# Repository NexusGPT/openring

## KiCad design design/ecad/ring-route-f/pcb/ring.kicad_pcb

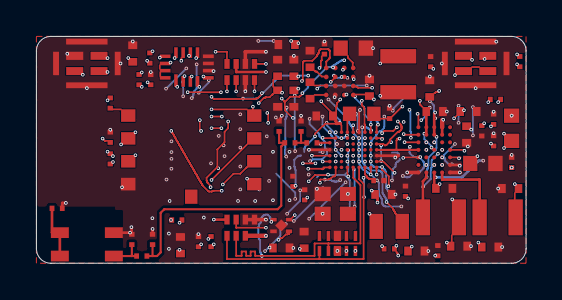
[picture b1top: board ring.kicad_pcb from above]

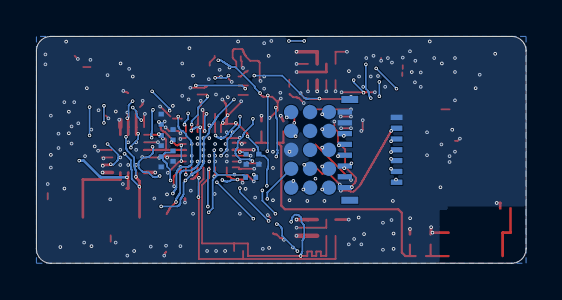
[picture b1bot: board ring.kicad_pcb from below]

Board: 4 copper layers, 27.2 x 12.6 mm, 100 parts (24 on the bottom side), 84 nets.

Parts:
ANT1: 2450AT18D0100001E; ANT_Johanson_2450AT18D0100001E_3.2x1.6
C1, C2, C5, C61, C72, C80, C81, C82: 100nF; Chip_0201
C3: 1.2pF; Chip_0201
C4, C22, C25, C74, C75, C78, C79, C83, C84: 10uF; Chip_0402
C6: 4.7uF; Chip_0201
C7, C10, C14: 2.2uF; Chip_0201
C11, C21, C26, C27: 4.7uF; Chip_0402
C12: 0.5pF; Chip_0201
C13, C89: DNP; Chip_0201
C23, C60, C85: 2.2uF; Chip_0402
C24, C88: 10uF; Chip_0603
C28, C29: 22uF; Chip_0402
C31, C32: 1uF; Chip_0201
C35, C36: 1nF C0G; Chip_0402
C71: 1.0uF 25V; Chip_0402
C73: 1.0uF; Chip_0201
C76, C77: 1.0nF; Chip_0201
C86, C87: 1.0uF; Chip_0402
FB1: 120R@100MHz; Chip_0201
J1: FH35C-15S-0.3SHW(50); FPC_Hirose_FH35C-15S-0.3SHW
J_BAND_A: flex tail A (joystick side) 8 pads; J_BAND_A_BOARD
J_BAND_B: flex tail B (other side) 7 pads; J_BAND_B_BOARD
L1: 4.7uH; L_TDK_MLZ1608_1.6x0.8
L2: 3.6nH; Chip_0201
L3: 4.7nH; Chip_0201
L4: 3.3nH; Chip_0201
L10, L71, L72: 2.2uH; L_Murata_1269AS-H_2.5x2.0
LT1: 0R; Chip_0201
R1: 2.2R; Chip_0603
R2: 220R; Chip_0201
R31, R32, R61: 100R; Chip_0201
R57, R58: 4.7k; Chip_0201
R60, R63, R64, R65, R71: 47k; Chip_0201
R62, R66: 100k; Chip_0201
R72: 150k; Chip_0201
TP1, TP3, TP4, TP5, TP6, TP8, TP9, TP11, TP12, TP14, TP15, TP17, TP18, TP19, TP21: pad; TESTPAD_0.8
U1: nRF54LM20A; WLCSP-61_nRF54LM20A-CAAA
U2: nPM1304; WLCSP-35_nPM1304-CAAA
U3: CSNP32GCR01-BOW; LGA-9_CSNP32GCR01-BOW_8.0x6.2
U4: SGM38046; WLCSP-16_SGM38046_2.0x2.0_P0.5
U5, U6: SPK0641HT4H-1; LGA-8_Knowles_SPK0641HT4H-1_3.0x4.0
U9: TPD4E05U06; USON-10_TPD4E05U06DQA
U10: SN74AXC4T774; UQFN-16_SN74AXC4T774RSV_1.8x2.6
U11: TLV75530P 3.0V; X2SON-4_TLV755xxPDQN_1.0x1.0
X1: 32MHz; XTAL_Kyocera_CX2016DB_2.0x1.6
X2: 32.768kHz; XTAL_TXC_9HT11_2.0x1.2

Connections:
ANT1_NODE: L2.1, U1.C1
ANT2_NODE: C3.1, L2.2, L3.1
ANT3_NODE: C12.1, C89.1, L3.2, L4.1
ANT_TRIM: ANT1.2, ANT1.3, LT1.1
BTN_REC: J_BAND_A.5, U1.H2
DBG_TX: TP1.1, U1.B4
DCC: L1.1, U1.A5
DECA: C7.1, C14.1, FB1.2, U1.A8, U1.B2
DECD: C6.1, FB1.1, L1.2, U1.A6
ELVDD: C25.1, J1.2, U4.D3
ELVSS: C28.1, C29.1, J1.1, U4.D4
GND: ANT1.4, C1.2, C2.2, C3.2, C4.2, C5.2, C6.2, C7.2, C10.2, C11.2, C12.2, C13.2, C14.2, C21.2, C22.2, C24.2, C25.2, C26.2, C27.2, C28.2, C29.2, C31.2, C32.2, C35.2, C36.2, C60.2, C61.2, C71.2, C72.2, C73.2, C74.2, C75.2, C76.2, C77.2, C78.2, C79.2, C80.2, C81.2, C82.2, C83.2, C84.2, C85.2, C86.2, C87.2, C88.2, C89.2, J1.13, J1.14, J1.15, J_BAND_A.6, J_BAND_A.8, J_BAND_B.2, J_BAND_B.7, LT1.2, R2.2, R62.2, R66.2, R71.2, R72.2, TP18.1, U1.A7, U1.D3, U1.E1, U1.F10, U2.A6, U2.A7, U2.E7, U3.4, U4.A3, U4.B2, U4.B3, U5.3, U5.5, U5.6, U5.7, U5.8, U6.5, U6.6, U6.7, U6.8, U9.3, U9.8, U10.6, U10.7, U10.8, U11.2, U11.5, X1.2
JOY_DOWN: J_BAND_A.2, U1.G2
JOY_LEFT: J_BAND_A.3, U1.G1
JOY_RIGHT: J_BAND_A.4, U1.G10
JOY_UP: J_BAND_A.1, U1.H1
LCD_CS: J1.9, U1.F7
LCD_DCX: J1.11, U1.G7
LCD_MOSI: J1.12, U1.G8
LCD_RST: J1.8, U1.H5
LCD_SCK: J1.10, U1.G9
LCD_TE: J1.7, U1.F4
MIC1_DATA: R31.1, U5.1
MIC2_DATA: R32.1, U6.1
MIC_A_CLK: U1.F1, U5.2, U6.2
MIC_A_DATA: R31.2, R32.2, U1.F2
MIC_B_DATA: TP21.1, U1.D7
MOTOR: R61.1, U1.F6
MOT_EN: R61.2, R62.1, U11.3
NRESET: TP5.1, U1.E2
NTC: J_BAND_B.3, U2.D3
OLED_PWR_EN: R66.1, U1.F9, U4.C2
PMIC_INT: U1.D8, U2.D6
PMIC_SCL: R58.1, U1.E7, U2.E3
PMIC_SDA: R57.1, U1.B8, U2.E5
RF_FEED: ANT1.1, C13.1, L4.2
SDC_CS: R65.1, U3.2, U10.10
SDC_MISO: R60.1, U3.6, U10.9
SDC_MOSI: U3.5, U10.11
SDC_SCK: U3.3, U10.12
SD_CS: U1.D9, U10.3
SD_DAT1: R63.1, U3.7
SD_DAT2: R64.1, U3.1
SD_MISO: U1.D10, U10.4
SD_MOSI: U1.B10, U10.2
SD_SCK: U1.A9, U10.1
SGM_AVDD: C26.1, U4.D2
SGM_AVIN: C22.1, U4.A2
SGM_C1N: C23.2, U4.B4
SGM_C1P: C23.1, U4.A4
SGM_SW1: L10.1, U4.B1
SGM_SW2: L10.2, U4.C1
SGM_VON: C27.1, U4.C4
SGM_VOUT: C24.1, U4.D1
SHPHLD: TP19.1, U2.D4
SPARE_P1_00: TP6.1, U1.H10
SPARE_P2_00: TP12.1, U1.A10
SPARE_P3_03: TP14.1, U1.F5
SPARE_P3_04: TP15.1, U1.G5
SW1: L71.1, U2.B7
SW2: L72.1, U2.D7
SWDCLK: TP3.1, U1.D5
SWDIO: TP4.1, U1.E4
SWIRE: J1.6, U4.C3
TXRTUNE: R2.1, U1.G6
U1_VBUS: C11.1, R1.2, U1.H9
USB_DN: J_BAND_B.5, U1.H6, U9.2
USB_DP: J_BAND_B.6, U1.H7, U9.1
VBAT: C21.1, C83.1, C85.1, J_BAND_B.1, U2.D1, U2.D2, U4.A1, U11.4
VBUS: C71.1, C72.1, J_BAND_B.4, R1.1, U2.B1, U2.B2, U9.4, U9.5
VBUSOUT: C73.1, U2.C3
VDD_1V8: C1.1, C2.1, C4.1, C5.1, C78.1, C80.1, C81.1, J1.5, L71.2, R57.2, R58.2, TP17.1, U1.A4, U1.E10, U2.B4, U2.B6, U2.E4, U10.5, U10.14, U10.15, U10.16
VDD_3V0: C79.1, J1.4, L72.2, U2.B5, U2.C6
VDD_MIC: C31.1, C32.1, C35.1, C36.1, C86.1, U2.A4, U5.4, U6.3, U6.4
VDD_SD: C60.1, C61.1, C82.1, C87.1, R60.2, R63.2, R64.2, R65.2, U2.A5, U3.8, U10.13
VDD_USB_3V3: C10.1, U1.H8
VMOT: C84.1, J_BAND_A.7, U11.1
VSET1: R71.1, U2.E2
VSET2: R72.1, U2.E1
VSYS: C74.1, C75.1, C76.1, C77.1, C88.1, U2.C1, U2.C2, U2.C7
XC1: U1.A2, X1.1
XC2: U1.A1, X1.3
XL1: U1.B6, X2.1
XL2: U1.B7, X2.2
